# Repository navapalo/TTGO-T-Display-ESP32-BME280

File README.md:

# TTGO-TDisplay-ESP32-BME280
ESP32 based temperature humidity pressure MQTT Sensor with TTGO-T-Display

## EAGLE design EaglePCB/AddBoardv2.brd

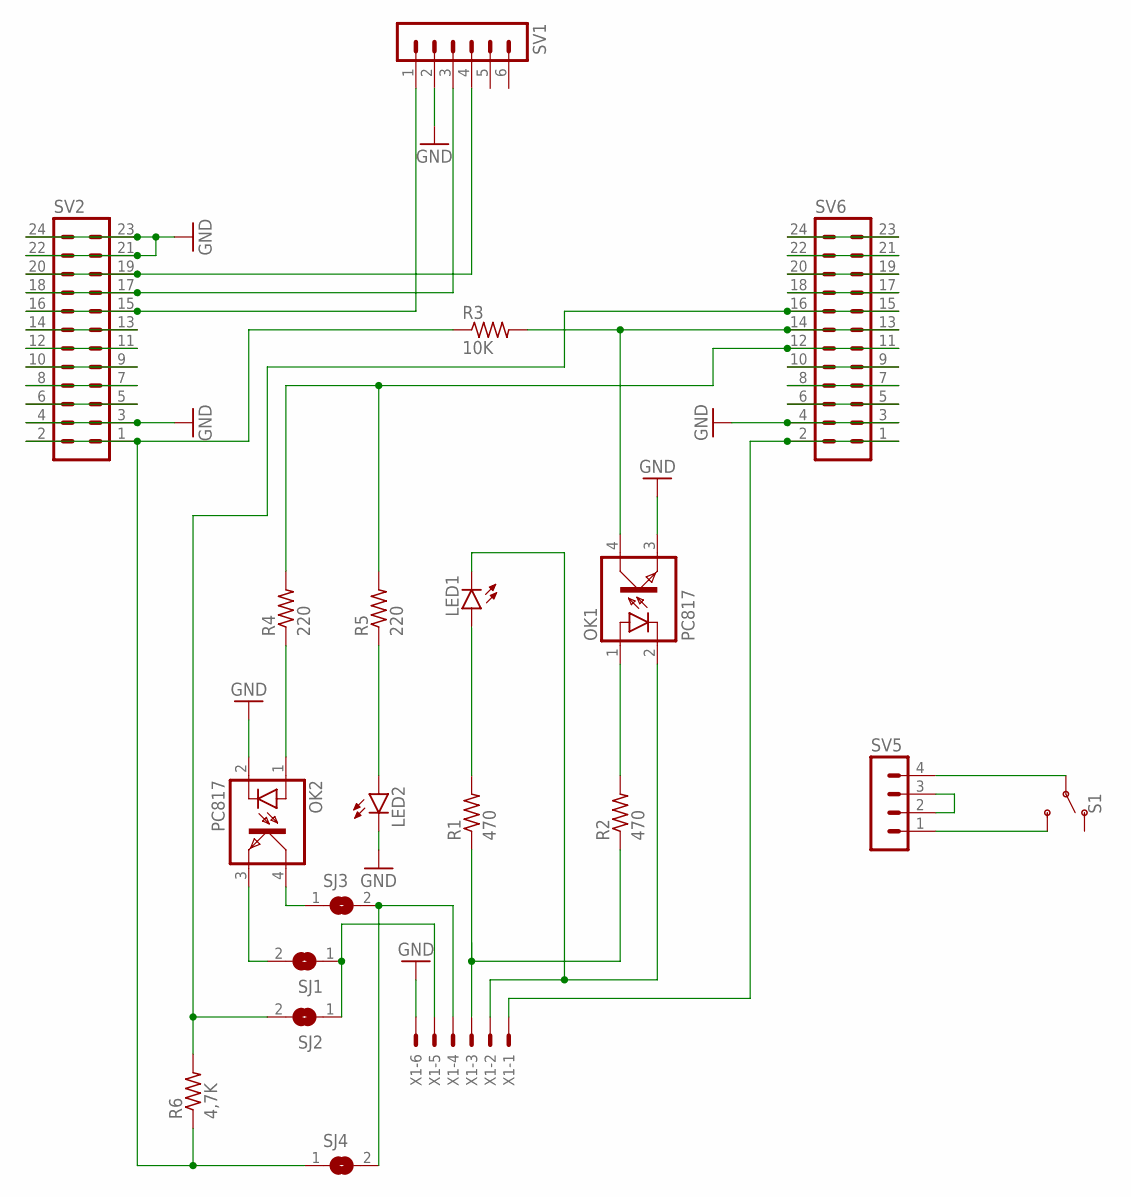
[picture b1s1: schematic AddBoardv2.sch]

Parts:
LED1, LED2: LEDCHIPLED_1206; CHIPLED_1206
OK1, OK2: PC817; DIL04
R1, R2: 470; RES_1206
R3: 10K; RES_1206
R4, R5: 220; RES_1206
R6: 4,7K; RES_1206
S1: SWITCH-SPDT-SMD-RIGHT-ANGLE; SWITCH_SPST_SMD_A
SJ1, SJ2, SJ3, SJ4: SJ
SV1: MA06-1
SV2, SV6: MA12-2
SV5: MA04-1
X1: 22-23-2061

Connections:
GND: LED2.C, OK1.3 (EMIT), OK2.2 (C), SV1.2, SV2.3, SV2.4, SV2.21, SV2.22, SV2.23, SV2.24, SV6.3, SV6.4, X1.6
unnamed: SV1.1, SV2.15, SV2.16
unnamed: SV1.3, SV2.17, SV2.18
unnamed: SV1.4, SV2.19, SV2.20
unnamed: SV6.1, SV6.2, X1.1
unnamed: LED1.C, OK1.2 (C), X1.2
unnamed: R1.1, R2.1, X1.3
unnamed: OK2.4 (COL), SJ3.1
unnamed: OK1.1 (A), R2.2
unnamed: LED1.A, R1.2
unnamed: R4.2, R5.2, SV6.11, SV6.12
unnamed: R3.1, R6.1, SJ4.1, SV2.1, SV2.2
unnamed: SJ3.2, SJ4.2, X1.4
unnamed: LED2.A, R5.1
unnamed: OK2.1 (A), R4.1
unnamed: OK1.4 (COL), R3.2, SV6.13, SV6.14
unnamed: SV2.5, SV2.6
unnamed: SV2.7, SV2.8
unnamed: SV2.9, SV2.10
unnamed: SV2.11, SV2.12
unnamed: SV2.13, SV2.14
unnamed: SV6.5, SV6.6
unnamed: SV6.7, SV6.8
unnamed: SV6.9, SV6.10
unnamed: R6.2, SJ2.2, SV6.15, SV6.16
unnamed: SV6.19, SV6.20
unnamed: SV6.21, SV6.22
unnamed: SV6.23, SV6.24
unnamed: SV5.2, SV5.3
unnamed: S1.2, SV5.4
unnamed: S1.3 (S), SV5.1
unnamed: OK2.3 (EMIT), SJ1.2
unnamed: SJ1.1, SJ2.1, X1.5
unnamed: SV6.17, SV6.18

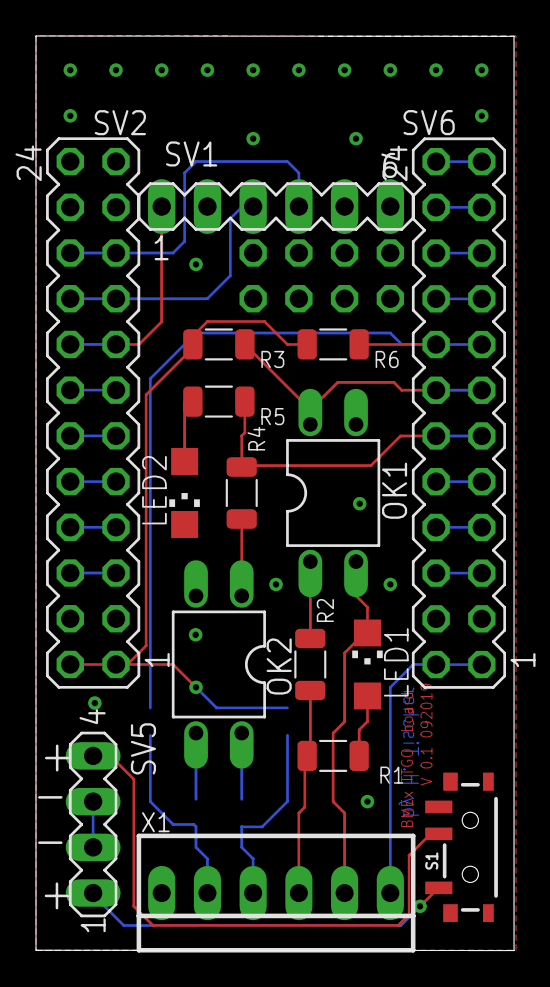
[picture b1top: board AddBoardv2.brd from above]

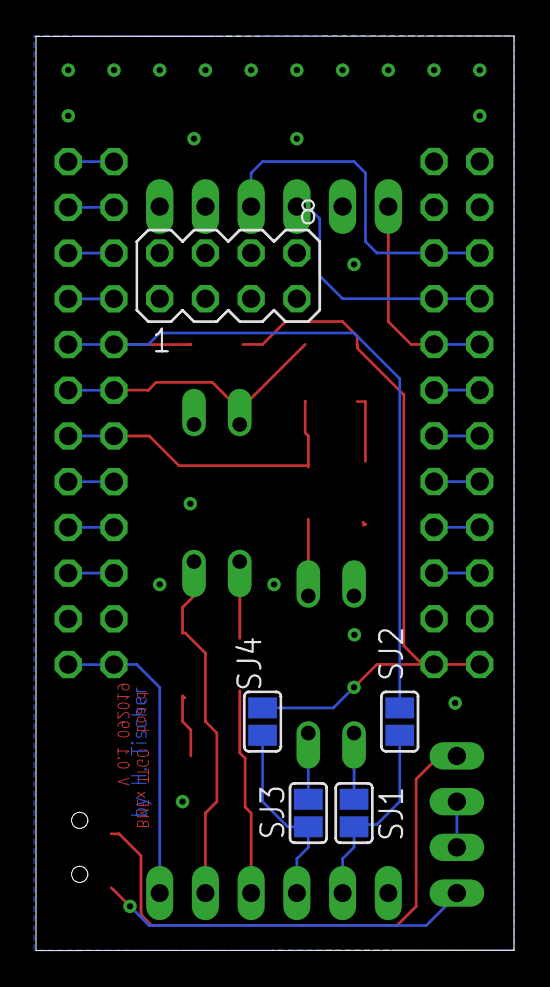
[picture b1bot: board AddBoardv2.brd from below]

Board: 2 copper layers, 26.6 x 50.8 mm, 21 parts (5 on the bottom side), 34 nets.

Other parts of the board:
SV3: MA04-2

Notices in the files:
parts and their libraries:
SparkFun-Switches: Licensing: Creative Commons ShareAlike 4.0 International - https://creativecommons.org/licenses/by-sa/4.0
